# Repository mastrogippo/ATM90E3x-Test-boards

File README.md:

## ATM90E36A and ATM90E32 PolyPhase energy measurement ICs testing boards

[Writeup and pics here](http://www.mastrogippo.it/2019/08/first-prototype-and-test-hardware/)

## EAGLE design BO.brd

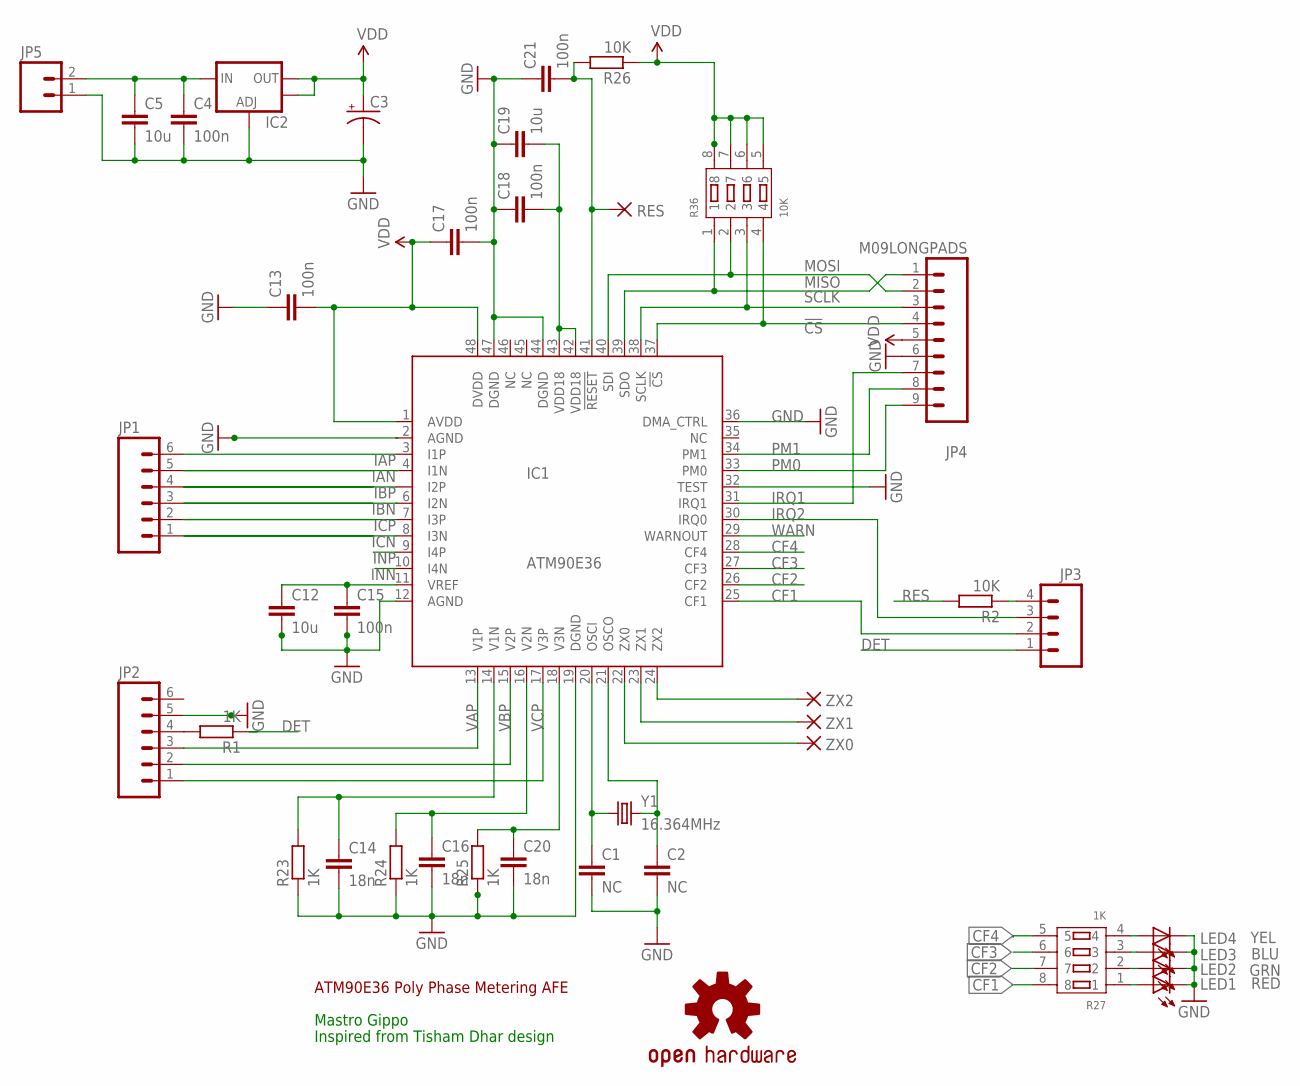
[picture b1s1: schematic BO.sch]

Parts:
C1, C2: NC; C0805K
C3: CPOL-USE5-6; E5-6
C4, C13, C15, C17, C18, C21: 100n; C0805K
C5, C12, C19: 10u; C0805K
C14, C16, C20: 18n; C0805K
IC1: ATM90E36; TQFP48
IC2: V_REG_LM1117SOT223; SOT223
JP1, JP2: M06LONGPADS; 1X06_LONGPADS
JP3: M04LONGPADS; 1X04_LONGPADS
JP4: M09LONGPADS; 1X09_LONGPADS
JP5: M02PTH3; 1X02_LONGPADS
LED1: RED; CHIP-LED0603
LED2: GRN; CHIP-LED0603
LED3: BLU; CHIP-LED0603
LED4: YEL; CHIP-LED0603
LOGO1: OSHW-LOGOM; OSHW-LOGO-M
R1, R23, R24, R25: 1K; M0805
R2, R26: 10K; M0805
R27: 1K; RA1206-8
R36: 10K; RA1206-8
RES: ZX0; SMD1,27-2,54
Y1: 16.364MHz; HC49UP
ZX0, ZX2: ZX0; SMD1,27-2,54
ZX1: ZX1; SMD1,27-2,54

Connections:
!CS: IC1.37 (!CS), JP4.4, R36.4
CF1: IC1.25 (CF1), JP3.2, R27.8
CF2: IC1.26 (CF2), R27.7
CF3: IC1.27 (CF3), R27.6
CF4: IC1.28 (CF4), R27.5
DET: JP3.1, R1.1
GND: C1.2, C2.2, C3.-, C4.2, C5.2, C12.2, C13.1, C14.2, C15.2, C16.2, C17.2, C18.1, C19.1, C20.2, C21.1, IC1.2 (AGND), IC1.12 (AGND), IC1.19 (DGND), IC1.32 (TEST), IC1.36 (DMA_CTRL), IC1.44 (DGND), IC1.47 (DGND), IC2.1 (ADJ), JP2.5, JP4.6, JP5.1, LED1.C, LED2.C, LED3.C, LED4.C, R23.1, R24.1, R25.1
IAN: IC1.4 (I1N), JP1.5
IAP: IC1.3 (I1P), JP1.6
IBN: IC1.6 (I2N), JP1.3
IBP: IC1.5 (I2P), JP1.4
ICN: IC1.8 (I3N), JP1.1
ICP: IC1.7 (I3P), JP1.2
INN: IC1.10 (I4N)
INP: IC1.9 (I4P)
IRQ1: IC1.31 (IRQ1), JP4.7
IRQ2: IC1.30 (IRQ0), JP3.3
MISO: IC1.39 (SDO), JP4.1, R36.1
MOSI: IC1.40 (SDI), JP4.2, R36.2
unnamed: JP3.4, R2.1
unnamed: JP2.4, R1.2
unnamed: LED4.A, R27.4
unnamed: LED3.A, R27.3
unnamed: LED2.A, R27.2
unnamed: LED1.A, R27.1
unnamed: C4.1, C5.1, IC2.3 (IN), JP5.2
unnamed: C1.1, IC1.20 (OSCI), Y1.1
unnamed: C2.1, IC1.21 (OSCO), Y1.2
unnamed: C14.1, IC1.14 (V1N), R23.2
unnamed: C16.1, IC1.16 (V2N), R24.2
unnamed: C20.1, IC1.18 (V3N), R25.2
unnamed: C18.2, C19.2, IC1.42 (VDD18), IC1.43 (VDD18)
unnamed: C12.1, C15.1, IC1.11 (VREF)
PM0: IC1.33 (PM0), JP4.9
PM1: IC1.34 (PM1), JP4.8
RES: C21.2, IC1.41 (!RESET), R2.2, R26.2, RES.1
SCLK: IC1.38 (SCLK), JP4.3, R36.3
VAP: IC1.13 (V1P), JP2.3
VBP: IC1.15 (V2P), JP2.2
VCP: IC1.17 (V3P), JP2.1
VDD: C3.+, C13.2, C17.1, IC1.1 (AVDD), IC1.48 (DVDD), IC2.2 (OUT), IC2.4 (OUT), JP4.5, R26.1, R36.5, R36.6, R36.7, R36.8
WARN: IC1.29 (WARNOUT)
ZX0: IC1.22 (ZX0), ZX0.1
ZX1: IC1.23 (ZX1), ZX1.1
ZX2: IC1.24 (ZX2), ZX2.1

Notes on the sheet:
ATM90E36 Poly Phase Metering AFE
Inspired from Tisham Dhar design
Mastro Gippo

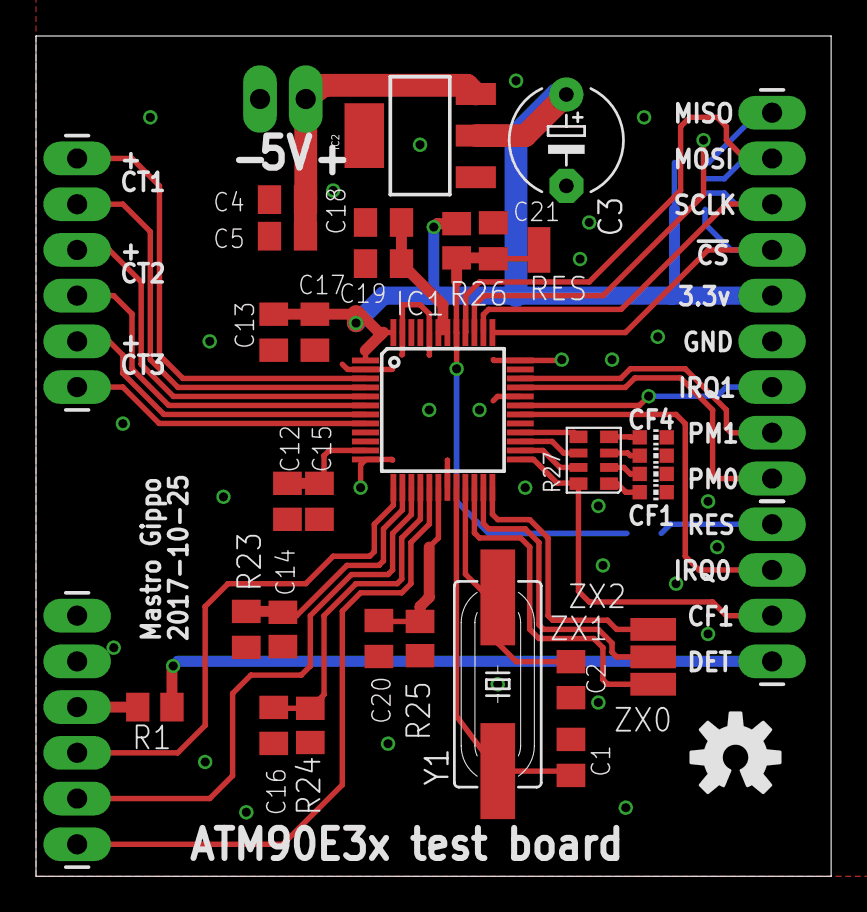
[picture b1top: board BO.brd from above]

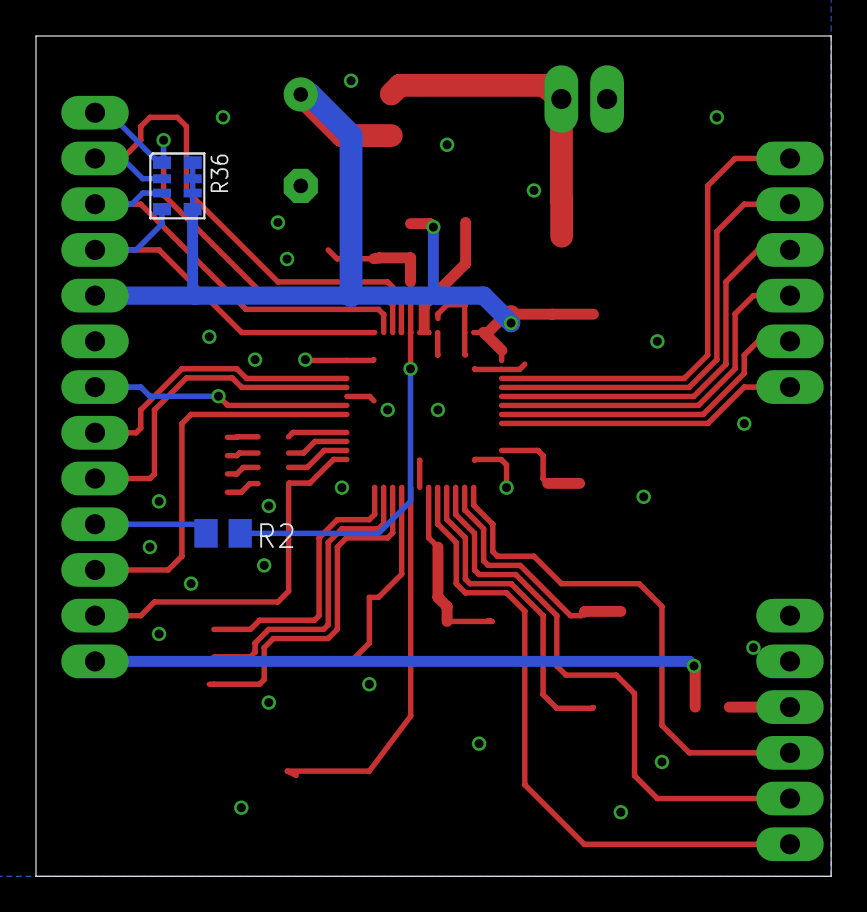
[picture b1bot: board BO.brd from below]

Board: 2 copper layers, 44.2 x 46.7 mm, 40 parts (2 on the bottom side), 42 nets.

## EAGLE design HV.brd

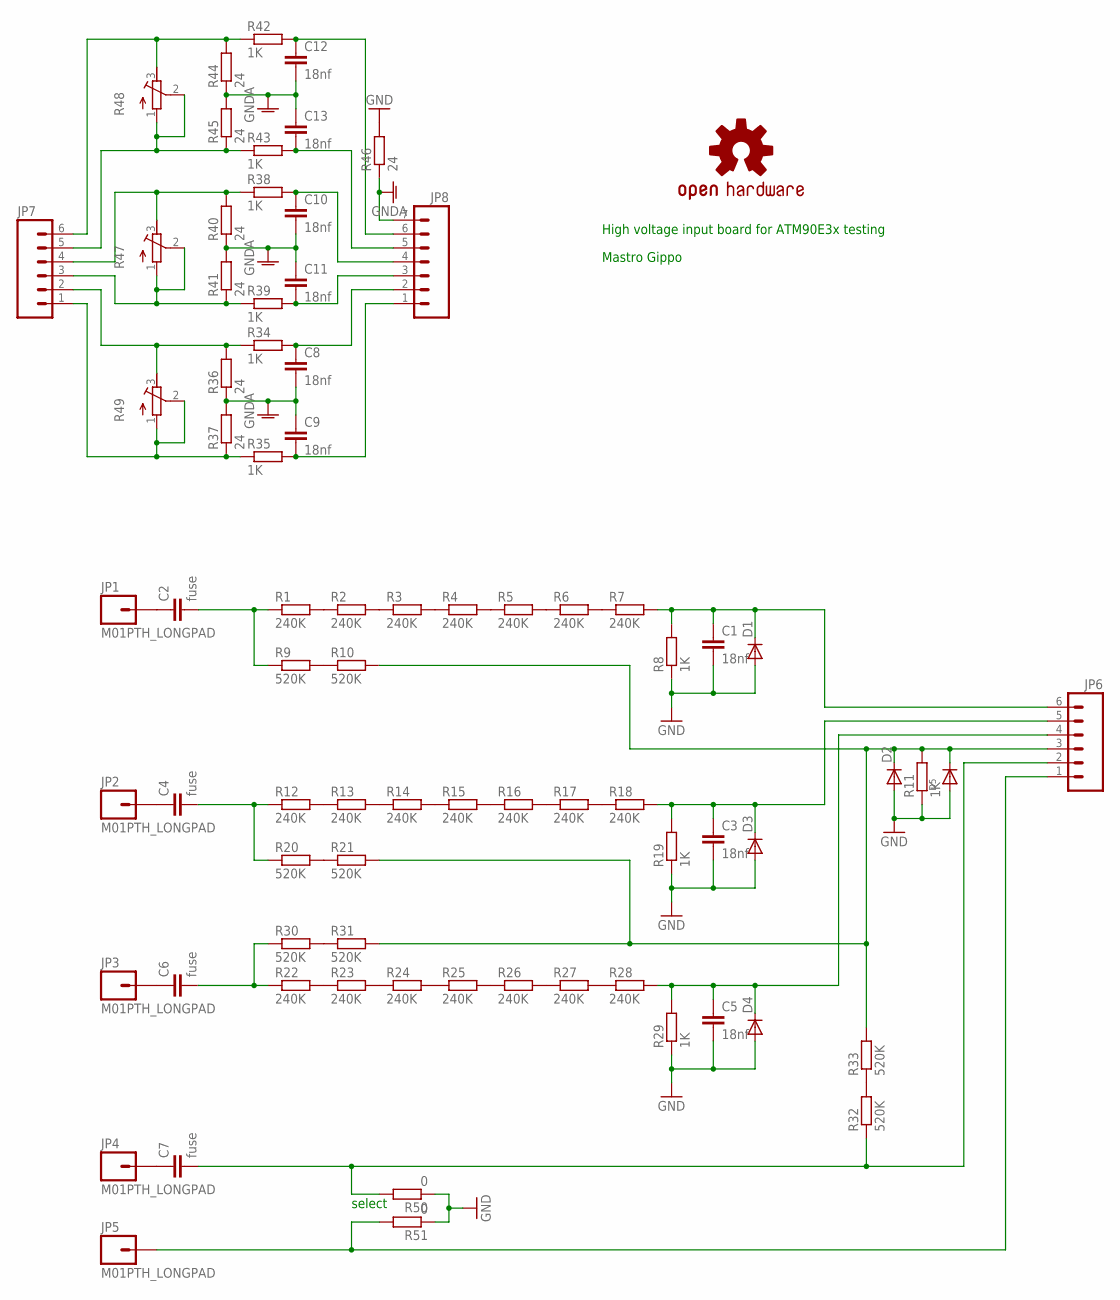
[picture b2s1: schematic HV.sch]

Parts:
C1, C3, C5, C8, C9, C10, C11, C12, C13: 18nf; C0805K
C2, C4, C6, C7: fuse; C050-025X075
D1, D2, D3, D4: DIODEHV; DIODE-HV
D5: DIODE_SOD-123FL; SOD-123FL
JP1, JP2, JP3, JP4, JP5: M01PTH_LONGPAD; 1X01_LONGPAD
JP6, JP7: M06LONGPADS; 1X06_LONGPADS
JP8: M07LONGPADS; 1X07_LONGPADS
R1, R2, R3, R4, R5, R6, R7, R12, R13, R14, R15, R16, R17, R18, R22, R23, R24, R25, R26, R27, R28: 240K; R0805
R8, R11, R19, R29, R34, R35, R38, R39, R42, R43: 1K; R0805
R9, R10, R20, R21, R30, R31, R32, R33: 520K; R0805
R36, R37, R40, R41, R44, R45, R46: 24; R0805
R47, R48, R49: R-TRIMM3224J; RTRIM3224J
R50, R51: 0; R0805
U$1: OSHW-LOGOS; OSHW-LOGO-S

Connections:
GND: C1.2, C3.2, C5.2, D1.A, D2.A, D3.A, D4.A, D5.A, R8.1, R11.1, R19.1, R29.1, R46.2, R50.1, R51.1
GNDA: C8.2, C9.1, C10.2, C11.1, C12.2, C13.1, JP8.7, R36.1, R37.2, R40.1, R41.2, R44.1, R45.2, R46.1
unnamed: C2.1, JP1.1
unnamed: R1.2, R2.1
unnamed: R2.2, R3.1
unnamed: R3.2, R4.1
unnamed: R4.2, R5.1
unnamed: R5.2, R6.1
unnamed: R6.2, R7.1
unnamed: C1.1, D1.C, JP6.6, R7.2, R8.2
unnamed: R9.2, R10.1
unnamed: C2.2, R1.1, R9.1
unnamed: R32.2, R33.1
unnamed: C3.1, D3.C, JP6.5, R18.2, R19.2
unnamed: C4.1, JP2.1
unnamed: C4.2, R12.1, R20.1
unnamed: R12.2, R13.1
unnamed: R13.2, R14.1
unnamed: R14.2, R15.1
unnamed: R15.2, R16.1
unnamed: R16.2, R17.1
unnamed: R17.2, R18.1
unnamed: R20.2, R21.1
unnamed: C7.1, JP4.1
unnamed: C5.1, D4.C, JP6.4, R28.2, R29.2
unnamed: C6.1, JP3.1
unnamed: C6.2, R22.1, R30.1
unnamed: R22.2, R23.1
unnamed: R23.2, R24.1
unnamed: R24.2, R25.1
unnamed: R25.2, R26.1
unnamed: R26.2, R27.1
unnamed: R27.2, R28.1
unnamed: R30.2, R31.1
unnamed: D2.C, D5.C, JP6.3, R10.2, R11.2, R21.2, R31.2, R33.2
unnamed: C7.2, JP6.2, R32.1, R50.2
unnamed: JP7.2, R34.1, R36.2, R49.3 (A)
unnamed: JP7.3, R39.1, R41.1, R47.1 (E), R47.2 (S)
unnamed: JP5.1, JP6.1, R51.2
unnamed: C8.1, JP8.2, R34.2
unnamed: C9.2, JP8.1, R35.2
unnamed: JP7.5, R43.1, R45.1, R48.1 (E), R48.2 (S)
unnamed: C10.1, JP8.4, R38.2
unnamed: JP7.1, R35.1, R37.1, R49.1 (E), R49.2 (S)
unnamed: JP7.6, R42.1, R44.2, R48.3 (A)
unnamed: C12.1, JP8.6, R42.2
unnamed: JP7.4, R38.1, R40.2, R47.3 (A)
unnamed: C11.2, JP8.3, R39.2
unnamed: C13.2, JP8.5, R43.2

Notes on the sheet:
select
High voltage input board for ATM90E3x testing
Mastro Gippo

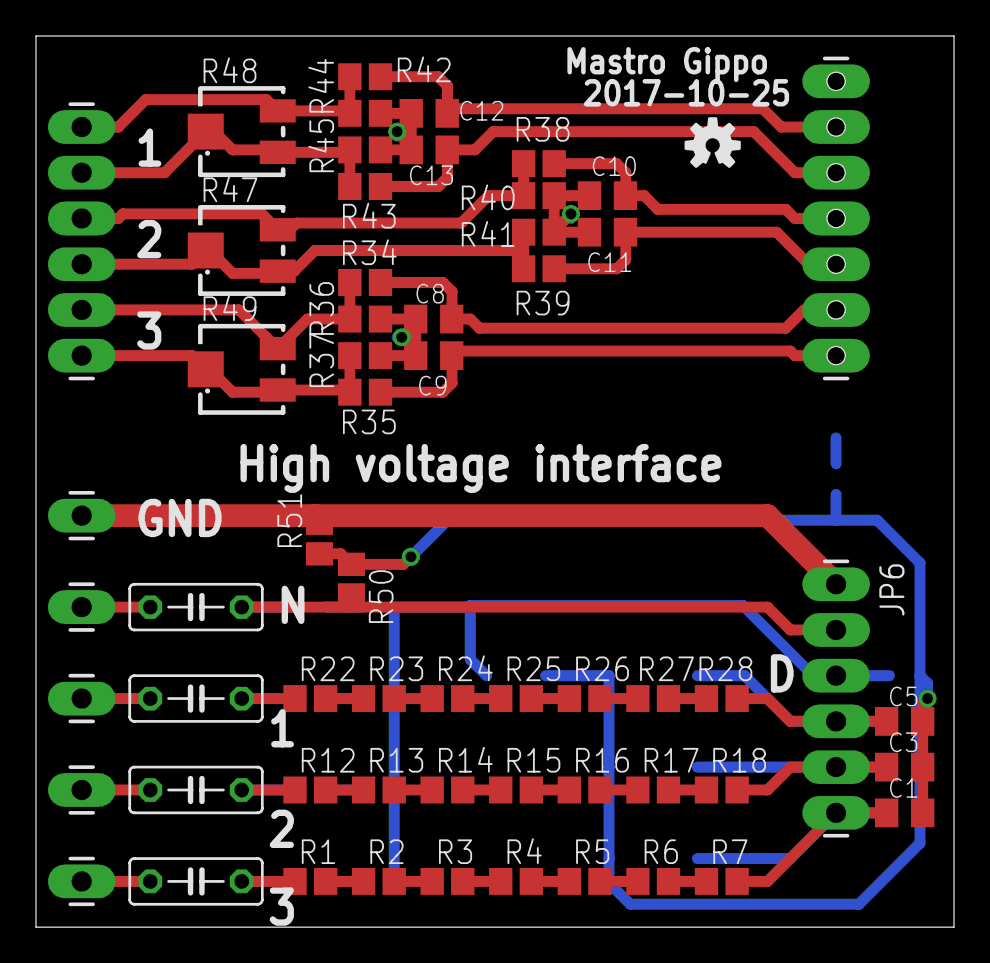
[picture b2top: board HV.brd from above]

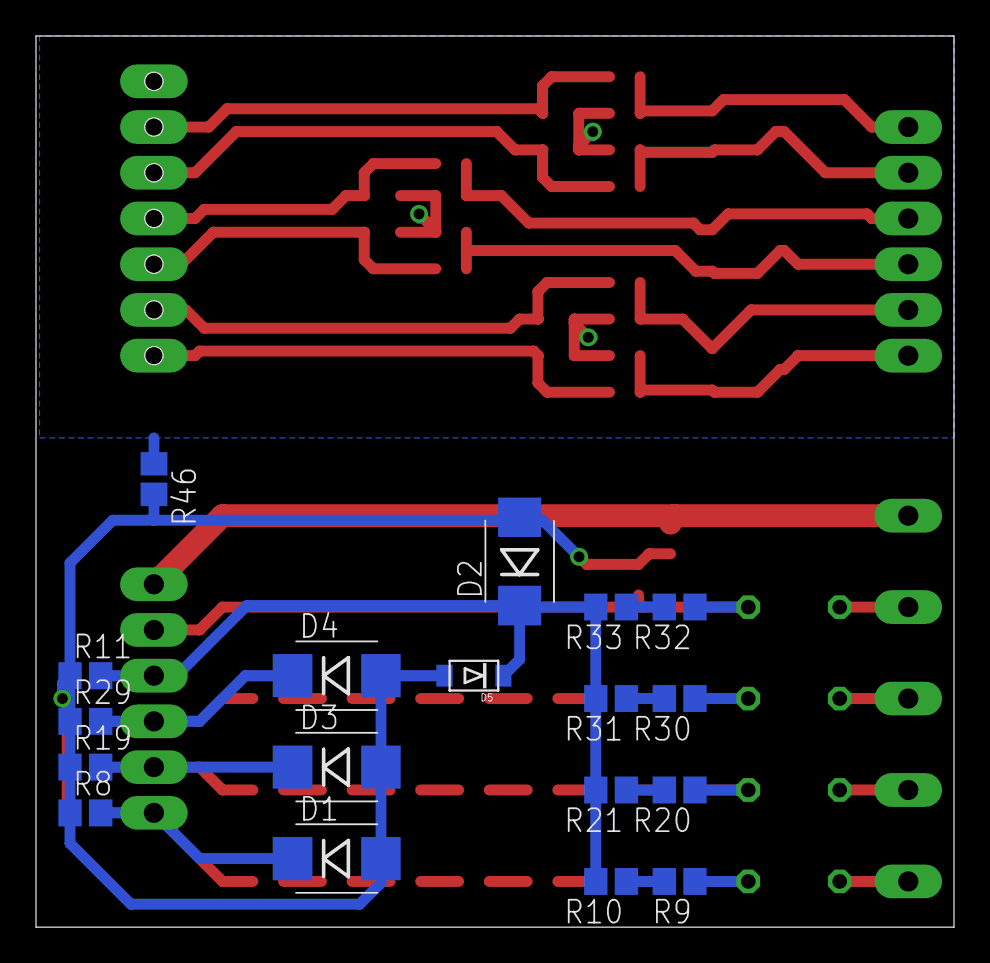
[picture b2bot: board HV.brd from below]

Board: 2 copper layers, 51.0 x 49.5 mm, 78 parts (18 on the bottom side), 49 nets.

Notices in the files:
parts and their libraries:
SparkFun: Licensing: CC v3.0 Share-Alike You are welcome to use this library for commercial purposes.
SparkFun-Aesthetics: Licensing: Creative Commons ShareAlike 4.0 International - https://creativecommons.org/licenses/by-sa/4.0
